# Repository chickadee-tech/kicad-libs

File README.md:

# Chickadee Tech Kicad Libs #
These are the Kicad components and footprints used in Chickadee Tech designs.

## Support ##
Use these components and footprints at your own risk!

## Contributing ##
Please note that this project is released with a [Contributor Code of Conduct](CODE_OF_CONDUCT.md). By participating in this project you agree to abide by its terms.

### Setup ###
Checkout this repository in the same directory that the board design repository is checked out in. All component libraries should use relative paths and not be installed globally so that they will load correctly.

### Pull requests ###
For fixes please submit a pull request to the original repository.

### Use in new designs ###
If developing your own board with these footprints DO NOT use Chickadee Tech trademarks (footprints/chickadee) and follow the [CC-BY license](LICENSE). While not required, please consider open sourcing your modifications so others can learn from your improvements.

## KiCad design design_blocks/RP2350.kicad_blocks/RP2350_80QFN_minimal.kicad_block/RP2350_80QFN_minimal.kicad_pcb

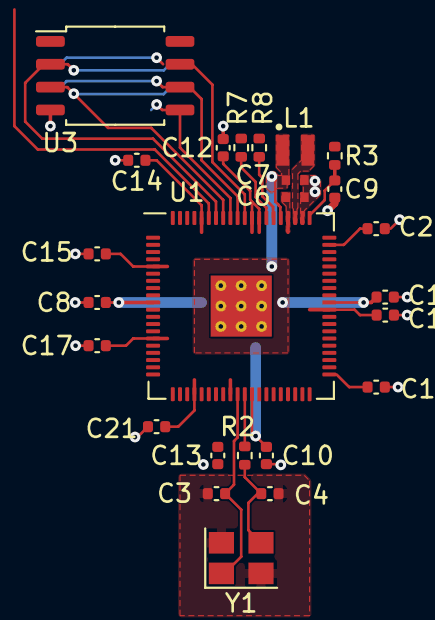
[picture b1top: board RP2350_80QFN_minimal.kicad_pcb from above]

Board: 2 copper layers, 25 parts (0 on the bottom side), 15 nets.

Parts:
C3, C4: 15p; C_0402_1005Metric
C6, C7: 4.7u; C_0402_1005Metric_small_pads
C8, C11, C12, C13, C14, C15, C16, C17, C18, C20, C21: 100n; C_0402_1005Metric
C9, C10: 4.7u; C_0402_1005Metric
L1: 3.3u; L_pol_2016
R2: 1k; R_0402_1005Metric
R3: 33; R_0402_1005Metric
R7, R8: 27; R_0402_1005Metric
U1: RP2350_80QFN; RP2350-QFN-80-1EP_10x10_P0.4mm_EP3.4x3.4mm_ThermalVias
U3: W25Q128JVS; SOIC-8_5.23x5.23mm_P1.27mm
Y1: ABM8-272-T3; Crystal_SMD_3225-4Pin_3.2x2.5mm

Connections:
+1V1: C7.1, C8.1, C10.1, C11.1, L1.1, U1.10 (DVDD), U1.32 (DVDD), U1.51 (DVDD), U1.65 (VREG_FB)
+3V3: C6.1, C12.1, C13.1, C14.1, C15.1, C16.1, C17.1, C18.1, C20.1, C21.1, R3.1, U1.5 (IOVDD), U1.15 (IOVDD), U1.24 (IOVDD), U1.29 (IOVDD), U1.41 (IOVDD), U1.50 (IOVDD), U1.59 (ADC_AVDD), U1.60 (IOVDD), U1.64 (VREG_VIN), U1.68 (USB_OTP_VDD), U1.69 (QSPI_IOVDD), U1.76 (IOVDD), U3.8 (VCC)
/QSPI_SCLK: U1.71 (QSPI_SCLK), U3.6 (CLK)
/QSPI_SD0: U1.72 (QSPI_SD0), U3.5 (DI(IO0))
/QSPI_SD1: U1.74 (QSPI_SD1), U3.2 (DO(IO1))
/QSPI_SD2: U1.73 (QSPI_SD2), U3.3 (IO2)
/QSPI_SD3: U1.70 (QSPI_SD3), U3.7 (IO3)
/VREG_AVDD: C9.1, R3.2, U1.61 (VREG_AVDD)
/VREG_LX: L1.2, U1.63 (VREG_LX)
/XIN: C3.1, U1.30 (XIN), Y1.1
/XOUT: R2.1, U1.31 (XOUT)
GND: C3.2, C4.2, C6.2, C7.2, C8.2, C9.2, C10.2, C11.2, C12.2, C13.2, C14.2, C15.2, C16.2, C17.2, C18.2, C20.2, C21.2, U1.62 (VREG_PGND), U1.81 (GND), U3.4 (GND), Y1.2, Y1.4
unnamed: C4.1, R2.2, Y1.3
unnamed: R8.2, U1.66 (USB_DM)
unnamed: R7.2, U1.67 (USB_DP)

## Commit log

2015-11-08 Shuffle around libraries so they are more easily shared.
2015-11-10 Create template and script to bootstrap expansion boards.
2015-11-18 receptacle for 20 pin power boards
2016-01-07 Add MPU-6500 component and Murata resonator footprint.
2016-01-26 More components and footprints for upcoming boards.
2016-01-30 v3 of pololu power. Moved pololu headers to the board edge, centered it to fit narrow standoffs, switched 5v traces to outside to hopefully strengthen the solder joint, and make annular ring of power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
2016-02-02 Add parts for new FCs and for bottom test jig.
2016-02-07 New footprint for quad XOR gate IC.
2016-03-05 More components and footprints including Fiducials for MacroFab and custom OSHW logo.
2016-03-14 More footprints
2016-04-07 Change USB to oval holes for MacroFab, add footprint for quad 2x1 mux and correct pins on power OR IC.
2016-04-13 New brand\! FlightStack is now Polystack because you can do more that just fly with a stack.
2016-04-13 Split up the center pad so it gets the amount of paste suggested on the datasheet.
2016-04-16 Initial work on M0 control board.
2016-04-16 Fix footprints for manufacture. Use baord edge for oval holes and adjust center of footprints to centroid of pads.
2016-07-07 Make the Chickadee footprints public. DO NOT use them on your own boards. The trademark is owned by Chickadee Tech.
2016-07-07 Add in Polystack connector component.
2016-07-07 Add components for STM32 chips.
2016-07-08 Update LICENSE
2016-07-08 Add README, LICENSE and code of conduct.
2017-09-10 Add parts for Feather RISC-V and ICE40
2017-09-11 Add ICE40UP5K
2018-03-02 New stuff for pyoven
2018-05-02 parts for feather trellis, gamegear and gameboy cartridge pcbs
2018-05-22 gamegear and mousebites
2019-03-09 Lotsa new things
2019-03-31 Add exposed pad to samd51, fixup usb and add paste-less test point.
2020-08-19 Add courtyard for SWD box
2020-09-24 Add mach xo2 symbol
2020-10-19 Michigan footprints
2021-01-01 Add usb a female
2021-02-10 more from old pcbs
2021-02-10 Add micromod
2021-02-14 Add 10FPC footprints
2021-02-15 10pos component
2021-02-15 hand solder neopixel
2021-02-16 veml7700
2021-03-25 Tabbed FPC
2021-07-04 molex 1x4 fpc
2026-06-09 RP2350B design block
